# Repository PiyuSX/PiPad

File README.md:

# PiPad

### A custom 3×3 mechanical macropad built from scratch.

## About

PiPad is a 3x3 macropad that I designed and build myself.It features 9 mechnical keys, a rotary encoder and an OLED display(128x32).

I started this project to get into Electronics and to learn PCB design , 3D CAD modelling and embedded firmware dev.

## Features

- 9 mechnical keys
- Rotary encoder
- OLED display 128x32
- 4 profiles
- 36 macros
- Custom QMK firmware

## Design

### PCB Design

Designed using KiCad

### 3D Enclosure

The enclosure was made in Fusin 360. I went through multiple versions to reduce the overall size and achieved a cleaner and minimal design.
It includes mounting points, a type C opening 

## Firmware

PiPad uses [QMK Firmware](https://github.com/qmk/qmk_firmware).

The firmware is configured with four profiles, each containing nine key positions, giving a total of 36 configurable macro positions.

The default key layout uses the F13–F21 key range.

```text
┌─────┬─────┬─────┐
│ F13 │ F14 │ F15 │
├─────┼─────┼─────┤
│ F16 │ F17 │ F18 │
├─────┼─────┼─────┤
│ F19 │ F20 │ F21 │
└─────┴─────┴─────┘
```

The firmware currently compiles successfully. Physical hardware testing is still pending.

## Development Journal

I documented the dev process, including the mistakes, redesigns and time spent on each process

**[Read the Development Journal →](JOURNAL.md)**

## Credits & Resources

- [QMK Firmware](https://github.com/qmk/qmk_firmware) – Keyboard firmware framework.
- [Joe Scotto's ScottoKicad](https://github.com/joe-scotto/scottokeebs/tree/main/Extras/ScottoKicad) – KiCad assets and resources used during PCB design.

## Bill of Materials

| Product | Qty | Price (USD) |
|---|---|---|
| Epomaker silent linear switches | 9 | $4.11 |
| Seeed XIAO RP2040 | 1 | $3.90 |
| 1N4148 diodes | 9 | $0.27 |
| Rotary encoder with push button | 1 | $1.30 |
| OLED 128x32 I2C display | 1 | $2.80 |
| Custom PCB (JLCPCB) | 1 | $4.00 |
| 3D printed case (JLC3DP), body + plate | 1 set | $4.00 |
| Blank black keycaps (MX) | 9 | $4.95 |
| M2 x 4 x 3.2 heat-set inserts | 4 | $0.13 |
| M2 x 5 screws | 4 | $0.24 |
| Aluminum encoder knob | 1 | $4.50 |
| **Total** | | **$30.20** |

Note: This price was last updated at 2026 NOV 

## Author

**Piyush Rajbanshi**

- Email: [hi@piyushrajbanshi.com.np](mailto:hi@piyushrajbanshi.com.np)

## License

This project is licensed under the [MIT License](LICENSE).

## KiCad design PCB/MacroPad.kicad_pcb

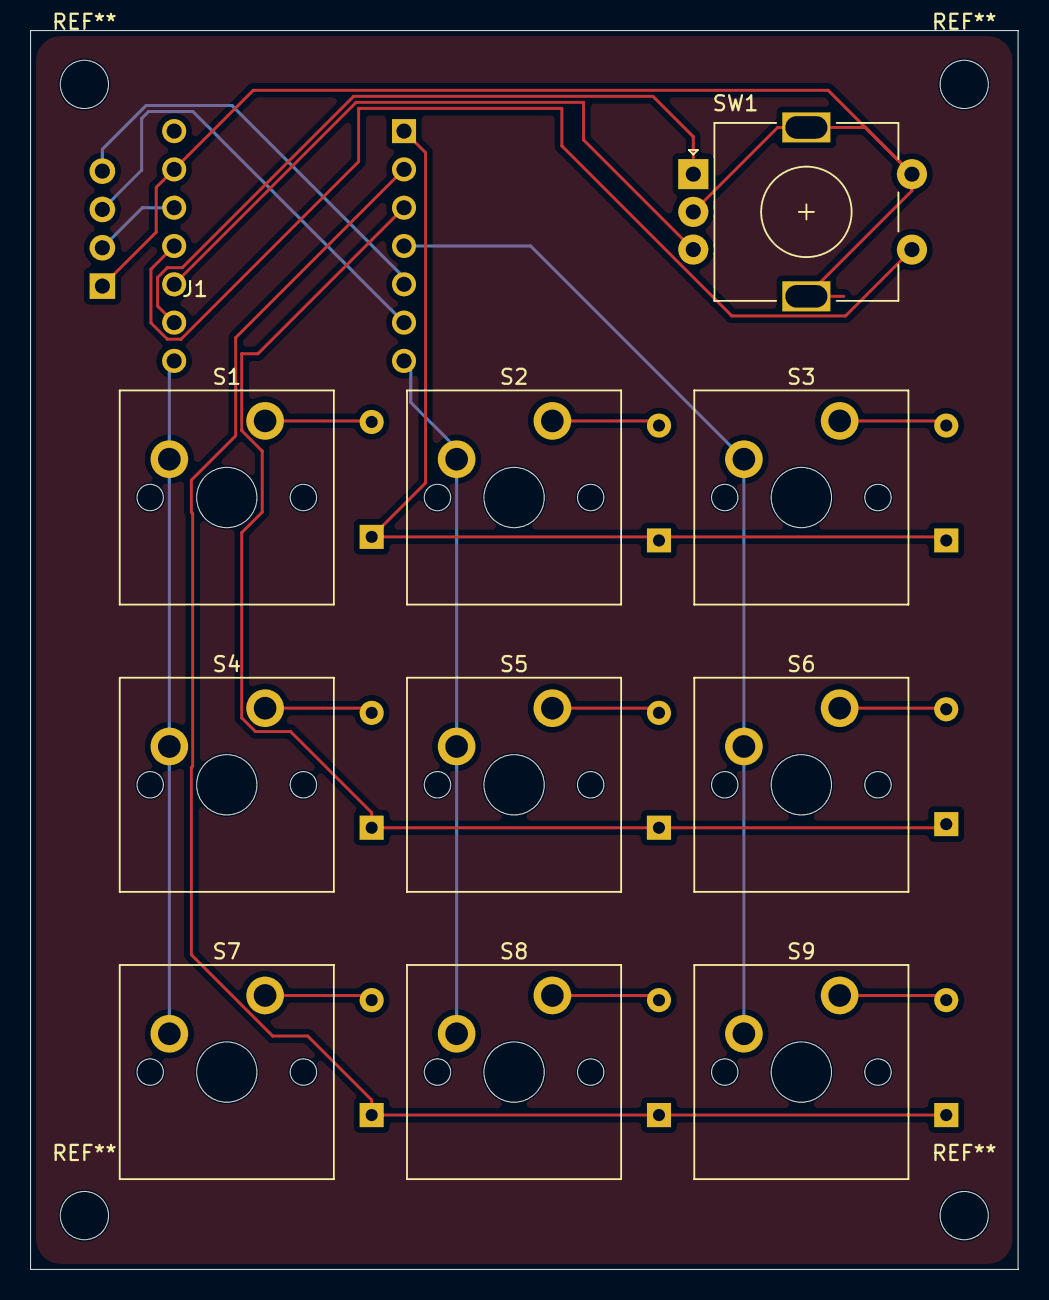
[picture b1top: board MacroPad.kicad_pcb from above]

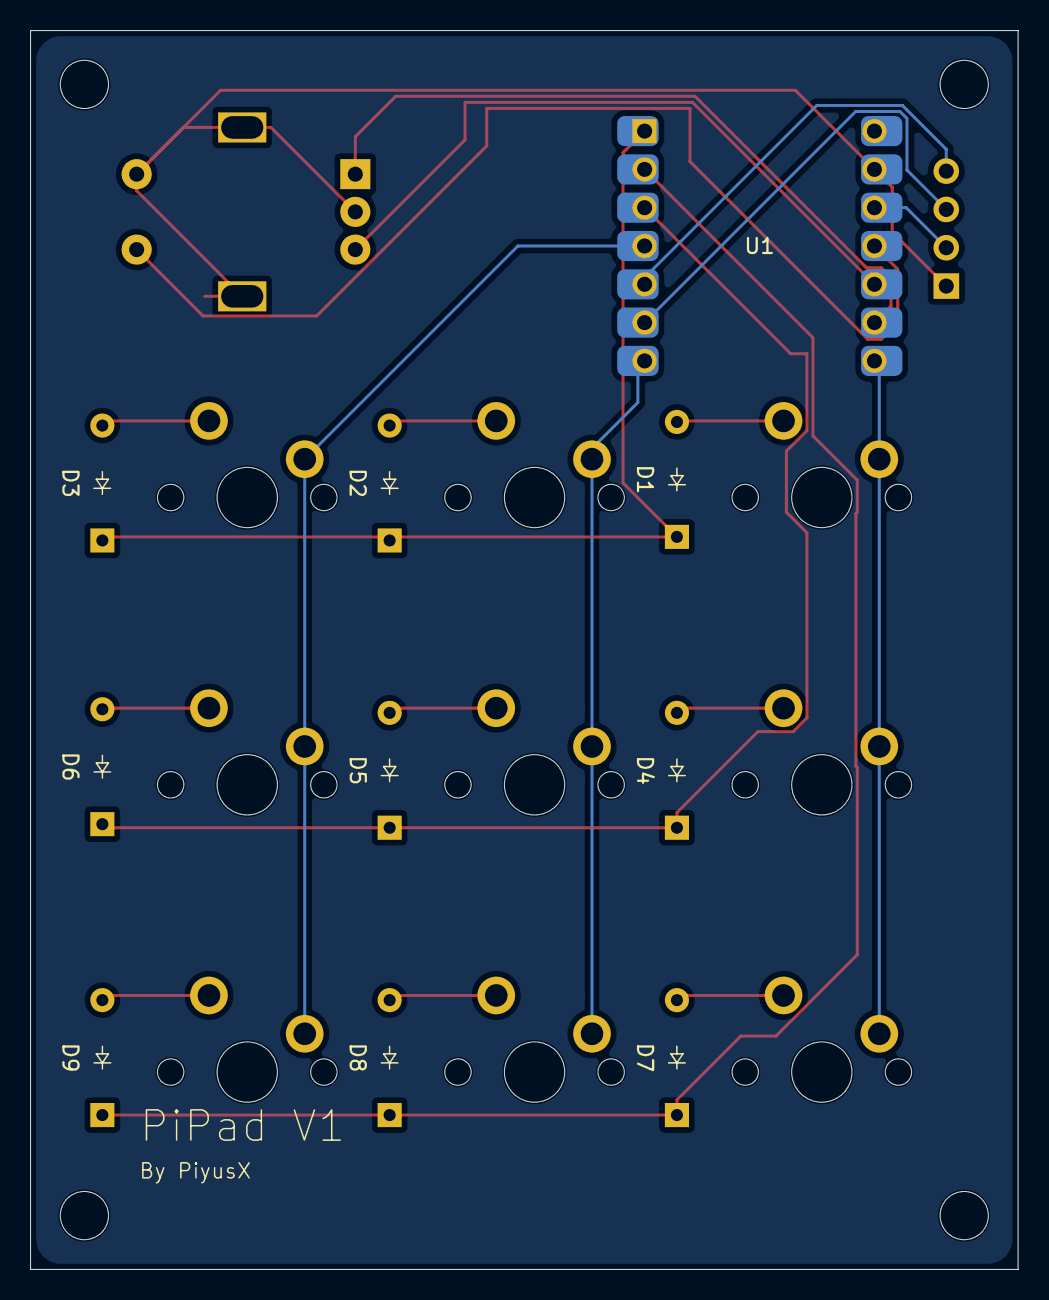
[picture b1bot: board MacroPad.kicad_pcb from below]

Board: 2 copper layers, 65.5 x 82.2 mm, 21 parts (10 on the bottom side), 22 nets.

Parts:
D1, D2, D3, D4, D5, D6, D7, D8, D9: Diode_DO-35
J1: OLED_128x32
S1, S2, S3, S4, S5, S6, S7, S8, S9: MX_PCB_1.00u
SW1: RotaryEncoder_Switch_MP; RotaryEncoder_Alps_EC11E-Switch_Vertical_H20mm
U1: MCU_Seeed_XIAO_RP2040; Seeed_XIAO_RP2040

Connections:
Column 0: S1.1, S4.1, S7.1, U1.8 (PB09_A7_D7_RX)
Column 1: S2.1, S5.1, S8.1, U1.7 (PB08_A6_D6_TX)
Column 2: S3.1, S6.1, S9.1, U1.4 (PA11_A3_D3)
ENC_A: SW1.A, U1.9 (PA7_A8_D8_SCK)
ENC_B: SW1.B, U1.10 (PA5_A9_D9_MISO)
ENC_SW: SW1.S1, U1.11 (PA6_A10_D10_MOSI)
unnamed: D1.2 (A), S1.2
unnamed: D2.2 (A), S2.2
unnamed: D3.2 (A), S3.2
unnamed: D4.2 (A), S4.2
unnamed: D5.2 (A), S5.2
unnamed: D6.2 (A), S6.2
unnamed: D7.2 (A), S7.2
unnamed: D8.2 (A), S8.2
unnamed: D9.2 (A), S9.2
OLED_GND: J1.1 (GND), SW1.C, SW1.MP, SW1.S2, U1.13 (GND)
OLED_SCL: J1.3 (SCL), U1.6 (PA9_A5_D5_SCL)
OLED_SDA: J1.4 (SDA), U1.5 (PA8_A4_D4_SDA)
OLED_VCC: J1.2 (VCC), U1.12 (3V3)
Row 0: D1.1 (K), D2.1 (K), D3.1 (K), U1.1 (PA02_A0_D0)
Row 1: D4.1 (K), D5.1 (K), D6.1 (K), U1.3 (PA10_A2_D2)
Row 2: D7.1 (K), D8.1 (K), D9.1 (K), U1.2 (PA4_A1_D1)
